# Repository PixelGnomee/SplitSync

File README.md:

# SplitSync
 83 key keyboard that is splitable

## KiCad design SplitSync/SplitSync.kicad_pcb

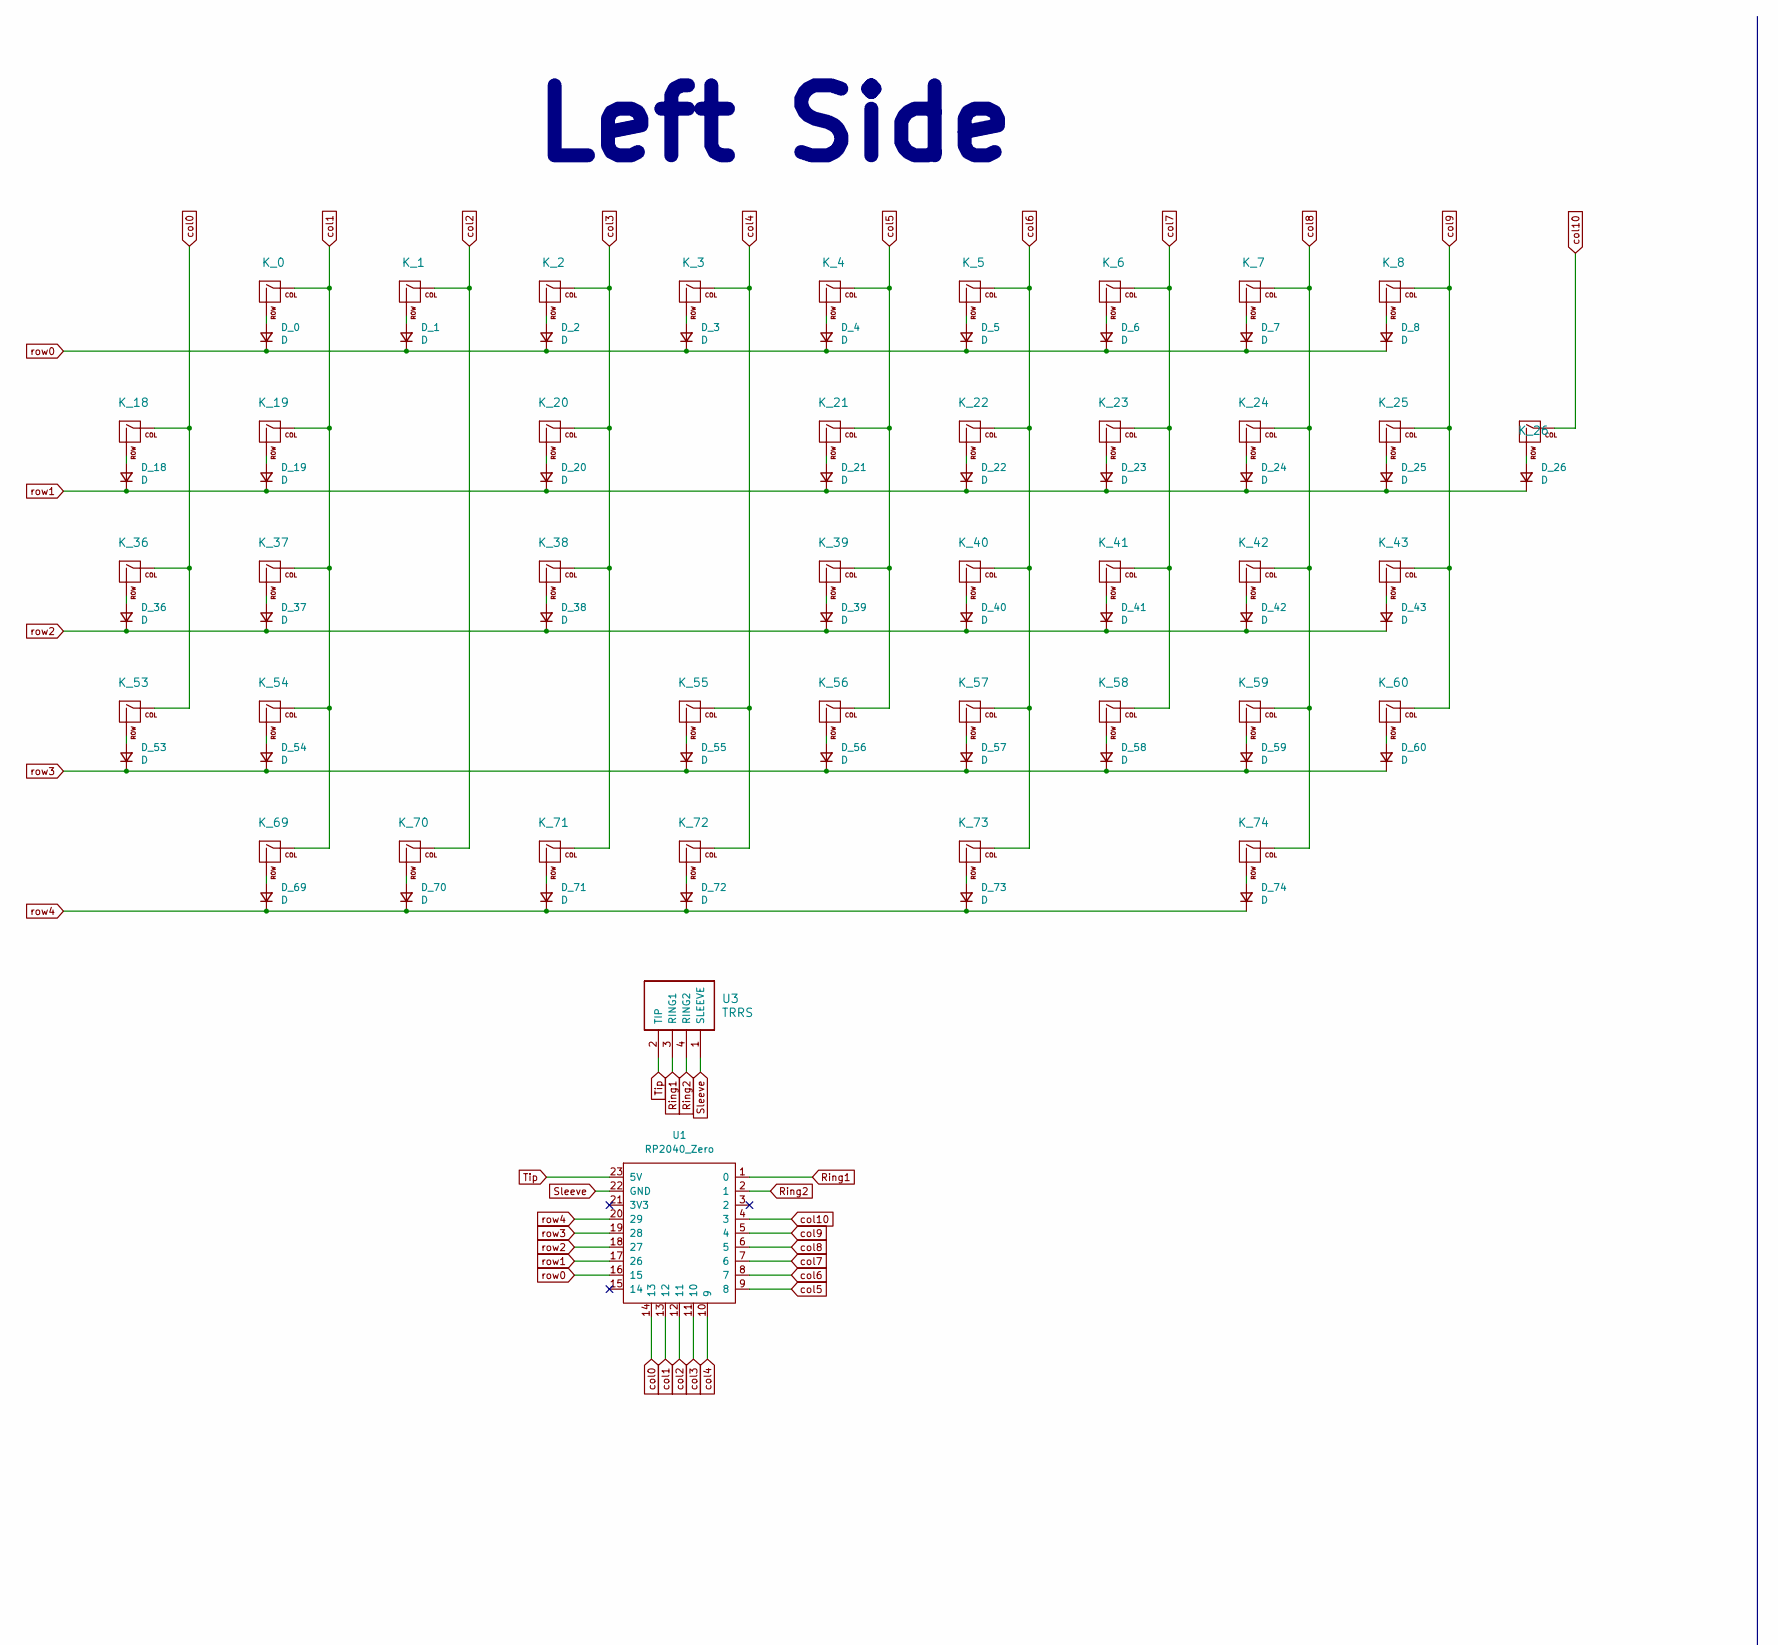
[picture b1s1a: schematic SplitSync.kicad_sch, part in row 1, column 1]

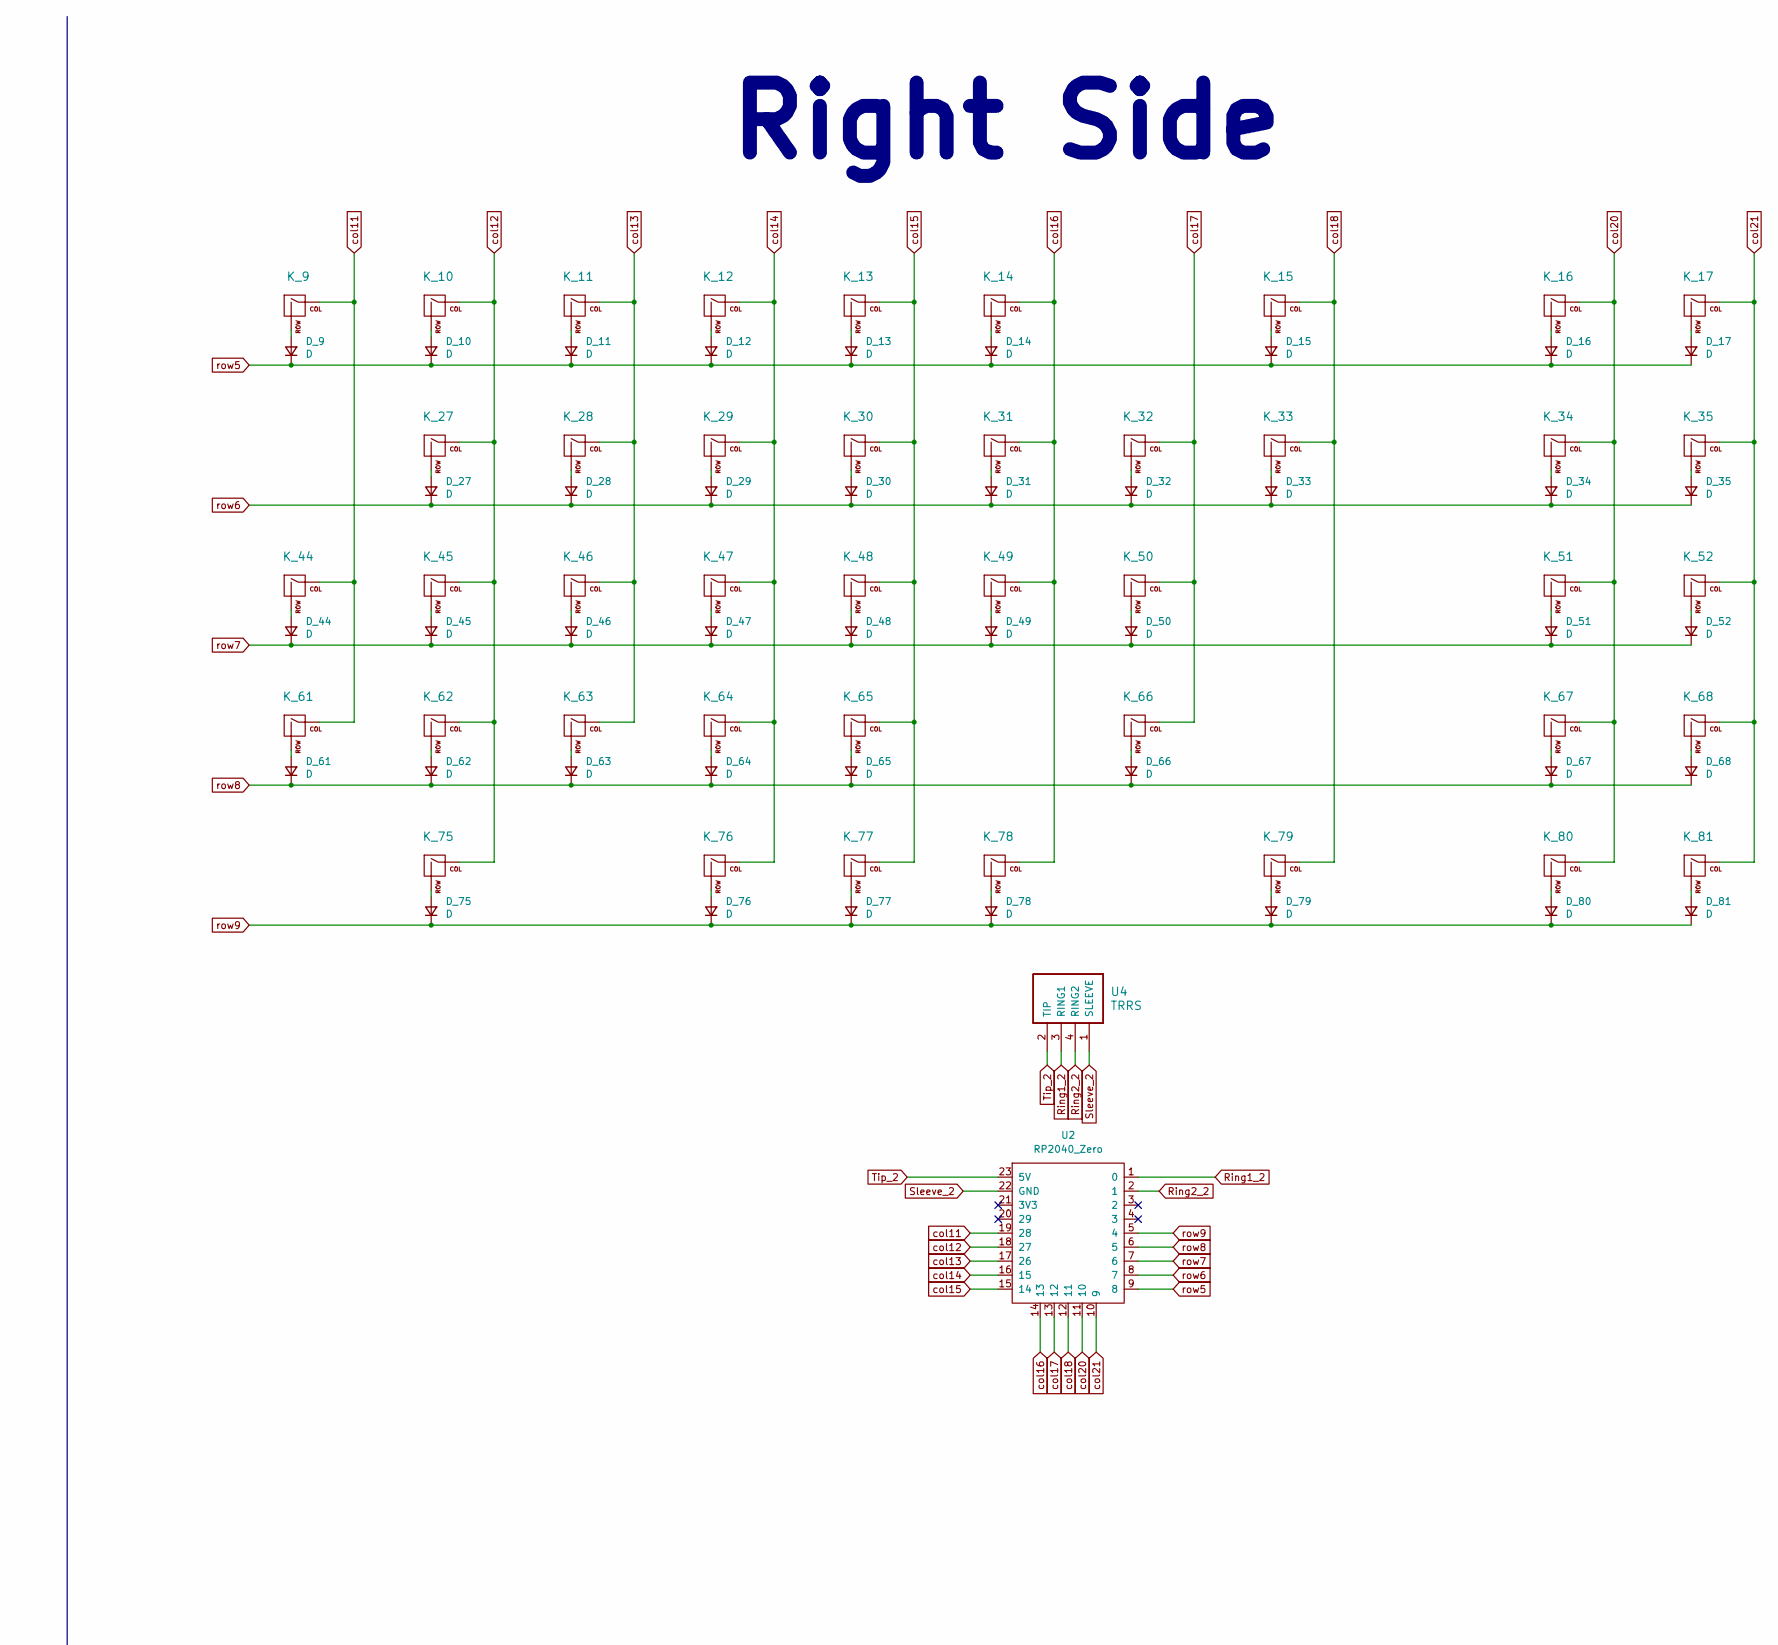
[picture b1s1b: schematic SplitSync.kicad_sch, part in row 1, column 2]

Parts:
D_0, D_1, D_2, D_3, D_4, D_5, D_6, D_7, D_8, D_9, D_10, D_11, D_12, D_13, D_14, D_15, D_16, D_17, D_18, D_19, D_20, D_21, D_22, D_23, D_24, D_25, D_26, D_27, D_28, D_29, D_30, D_31, D_32, D_33, D_34, D_35, D_36, D_37, D_38, D_39, D_40, D_41, D_42, D_43, D_44, D_45, D_46, D_47, D_48, D_49, D_50, D_51, D_52, D_53, D_54, D_55, D_56, D_57, D_58, D_59, D_60, D_61, D_62, D_63, D_64, D_65, D_66, D_67, D_68, D_69, D_70, D_71, D_72, D_73, D_74, D_75, D_76, D_77, D_78, D_79, D_80, D_81: D; D_SOD-123
K_0, K_1, K_2, K_3, K_4, K_5, K_6, K_7, K_8, K_9, K_10, K_11, K_12, K_13, K_14, K_15, K_16, K_17, K_18, K_19, K_21, K_22, K_23, K_24, K_25, K_26, K_27, K_28, K_29, K_30, K_31, K_32, K_34, K_35, K_36, K_37, K_39, K_40, K_41, K_42, K_43, K_44, K_45, K_46, K_47, K_48, K_49, K_51, K_52, K_53, K_54, K_56, K_57, K_58, K_59, K_60, K_61, K_62, K_63, K_64, K_65, K_67, K_68, K_69, K_70, K_80, K_81: KEYSW; Hotswap_MX_Plated_1.00u
K_20, K_33, K_79: KEYSW; Hotswap_MX_Plated_1.50u
K_38: KEYSW; Hotswap_MX_Plated_1.75u
K_50, K_55: KEYSW; Hotswap_MX_Plated_2.25u
K_66: KEYSW; Hotswap_MX_Plated_2.75u
K_71, K_72, K_73, K_76, K_77, K_78: KEYSW; Hotswap_MX_Plated_1.25u
K_74, K_75: KEYSW; Hotswap_MX_Plated_3.00u
U1, U2: RP2040_Zero
U3, U4: TRRS; TRRS_PJ-320A

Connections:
unnamed: D_0.2 (A), K_0.2 (ROW)
unnamed: D_1.2 (A), K_1.2 (ROW)
unnamed: D_2.2 (A), K_2.2 (ROW)
unnamed: D_3.2 (A), K_3.2 (ROW)
unnamed: D_4.2 (A), K_4.2 (ROW)
unnamed: D_5.2 (A), K_5.2 (ROW)
unnamed: D_6.2 (A), K_6.2 (ROW)
unnamed: D_7.2 (A), K_7.2 (ROW)
unnamed: D_8.2 (A), K_8.2 (ROW)
unnamed: D_9.2 (A), K_9.2 (ROW)
unnamed: D_10.2 (A), K_10.2 (ROW)
unnamed: D_11.2 (A), K_11.2 (ROW)
unnamed: D_12.2 (A), K_12.2 (ROW)
unnamed: D_13.2 (A), K_13.2 (ROW)
unnamed: D_14.2 (A), K_14.2 (ROW)
unnamed: D_15.2 (A), K_15.2 (ROW)
unnamed: D_16.2 (A), K_16.2 (ROW)
unnamed: D_17.2 (A), K_17.2 (ROW)
unnamed: D_18.2 (A), K_18.2 (ROW)
unnamed: D_19.2 (A), K_19.2 (ROW)
unnamed: D_20.2 (A), K_20.2 (ROW)
unnamed: D_21.2 (A), K_21.2 (ROW)
unnamed: D_22.2 (A), K_22.2 (ROW)
unnamed: D_23.2 (A), K_23.2 (ROW)
unnamed: D_24.2 (A), K_24.2 (ROW)
unnamed: D_25.2 (A), K_25.2 (ROW)
unnamed: D_26.2 (A), K_26.2 (ROW)
unnamed: D_27.2 (A), K_27.2 (ROW)
unnamed: D_28.2 (A), K_28.2 (ROW)
unnamed: D_29.2 (A), K_29.2 (ROW)
unnamed: D_30.2 (A), K_30.2 (ROW)
unnamed: D_31.2 (A), K_31.2 (ROW)
unnamed: D_32.2 (A), K_32.2 (ROW)
unnamed: D_33.2 (A), K_33.2 (ROW)
unnamed: D_34.2 (A), K_34.2 (ROW)
unnamed: D_35.2 (A), K_35.2 (ROW)
unnamed: D_36.2 (A), K_36.2 (ROW)
unnamed: D_37.2 (A), K_37.2 (ROW)
unnamed: D_38.2 (A), K_38.2 (ROW)
unnamed: D_39.2 (A), K_39.2 (ROW)
unnamed: D_40.2 (A), K_40.2 (ROW)
unnamed: D_41.2 (A), K_41.2 (ROW)
unnamed: D_42.2 (A), K_42.2 (ROW)
unnamed: D_43.2 (A), K_43.2 (ROW)
unnamed: D_44.2 (A), K_44.2 (ROW)
unnamed: D_45.2 (A), K_45.2 (ROW)
unnamed: D_46.2 (A), K_46.2 (ROW)
unnamed: D_47.2 (A), K_47.2 (ROW)
unnamed: D_48.2 (A), K_48.2 (ROW)
unnamed: D_49.2 (A), K_49.2 (ROW)
unnamed: D_50.2 (A), K_50.2 (ROW)
unnamed: D_51.2 (A), K_51.2 (ROW)
unnamed: D_52.2 (A), K_52.2 (ROW)
unnamed: D_53.2 (A), K_53.2 (ROW)
unnamed: D_54.2 (A), K_54.2 (ROW)
unnamed: D_55.2 (A), K_55.2 (ROW)
unnamed: D_56.2 (A), K_56.2 (ROW)
unnamed: D_57.2 (A), K_57.2 (ROW)
unnamed: D_58.2 (A), K_58.2 (ROW)
unnamed: D_59.2 (A), K_59.2 (ROW)
unnamed: D_60.2 (A), K_60.2 (ROW)
unnamed: D_61.2 (A), K_61.2 (ROW)
unnamed: D_62.2 (A), K_62.2 (ROW)
unnamed: D_63.2 (A), K_63.2 (ROW)
unnamed: D_64.2 (A), K_64.2 (ROW)
unnamed: D_65.2 (A), K_65.2 (ROW)
unnamed: D_66.2 (A), K_66.2 (ROW)
unnamed: D_67.2 (A), K_67.2 (ROW)
unnamed: D_68.2 (A), K_68.2 (ROW)
unnamed: D_69.2 (A), K_69.2 (ROW)
unnamed: D_70.2 (A), K_70.2 (ROW)
unnamed: D_71.2 (A), K_71.2 (ROW)
unnamed: D_72.2 (A), K_72.2 (ROW)
unnamed: D_73.2 (A), K_73.2 (ROW)
unnamed: D_74.2 (A), K_74.2 (ROW)
unnamed: D_75.2 (A), K_75.2 (ROW)
unnamed: D_76.2 (A), K_76.2 (ROW)
unnamed: D_77.2 (A), K_77.2 (ROW)
unnamed: D_78.2 (A), K_78.2 (ROW)
unnamed: D_79.2 (A), K_79.2 (ROW)
unnamed: D_80.2 (A), K_80.2 (ROW)
unnamed: D_81.2 (A), K_81.2 (ROW)
Ring1: U1.1 (0), U3.3 (RING1)
Ring1_2: U2.1 (0), U4.3 (RING1)
Ring2: U1.2 (1), U3.4 (RING2)
Ring2_2: U2.2 (1), U4.4 (RING2)
Sleeve: U1.22 (GND), U3.1 (SLEEVE)
Sleeve_2: U2.22 (GND), U4.1 (SLEEVE)
Tip: U1.23 (5V), U3.2 (TIP)
Tip_2: U2.23 (5V), U4.2 (TIP)
col0: K_18.1 (COL), K_36.1 (COL), K_53.1 (COL), U1.14 (13)
col1: K_0.1 (COL), K_19.1 (COL), K_37.1 (COL), K_54.1 (COL), K_69.1 (COL), U1.13 (12)
col2: K_1.1 (COL), K_70.1 (COL), U1.12 (11)
col3: K_2.1 (COL), K_20.1 (COL), K_38.1 (COL), K_71.1 (COL), U1.11 (10)
col4: K_3.1 (COL), K_55.1 (COL), K_72.1 (COL), U1.10 (9)
col5: K_4.1 (COL), K_21.1 (COL), K_39.1 (COL), K_56.1 (COL), U1.9 (8)
col6: K_5.1 (COL), K_22.1 (COL), K_40.1 (COL), K_57.1 (COL), K_73.1 (COL), U1.8 (7)
col7: K_6.1 (COL), K_23.1 (COL), K_41.1 (COL), K_58.1 (COL), U1.7 (6)
col8: K_7.1 (COL), K_24.1 (COL), K_42.1 (COL), K_59.1 (COL), K_74.1 (COL), U1.6 (5)
col9: K_8.1 (COL), K_25.1 (COL), K_43.1 (COL), K_60.1 (COL), U1.5 (4)
col10: K_26.1 (COL), U1.4 (3)
col11: K_9.1 (COL), K_44.1 (COL), K_61.1 (COL), U2.19 (28)
col12: K_10.1 (COL), K_27.1 (COL), K_45.1 (COL), K_62.1 (COL), K_75.1 (COL), U2.18 (27)
col13: K_11.1 (COL), K_28.1 (COL), K_46.1 (COL), K_63.1 (COL), U2.17 (26)
col14: K_12.1 (COL), K_29.1 (COL), K_47.1 (COL), K_64.1 (COL), K_76.1 (COL), U2.16 (15)
col15: K_13.1 (COL), K_30.1 (COL), K_48.1 (COL), K_65.1 (COL), K_77.1 (COL), U2.15 (14)
col16: K_14.1 (COL), K_31.1 (COL), K_49.1 (COL), K_78.1 (COL), U2.14 (13)
col17: K_32.1 (COL), K_50.1 (COL), K_66.1 (COL), U2.13 (12)
col18: K_15.1 (COL), K_33.1 (COL), K_79.1 (COL), U2.12 (11)
col20: K_16.1 (COL), K_34.1 (COL), K_51.1 (COL), K_67.1 (COL), K_80.1 (COL), U2.11 (10)
col21: K_17.1 (COL), K_35.1 (COL), K_52.1 (COL), K_68.1 (COL), K_81.1 (COL), U2.10 (9)
row0: D_0.1 (K), D_1.1 (K), D_2.1 (K), D_3.1 (K), D_4.1 (K), D_5.1 (K), D_6.1 (K), D_7.1 (K), D_8.1 (K), U1.16 (15)
row1: D_18.1 (K), D_19.1 (K), D_20.1 (K), D_21.1 (K), D_22.1 (K), D_23.1 (K), D_24.1 (K), D_25.1 (K), D_26.1 (K), U1.17 (26)
row2: D_36.1 (K), D_37.1 (K), D_38.1 (K), D_39.1 (K), D_40.1 (K), D_41.1 (K), D_42.1 (K), D_43.1 (K), U1.18 (27)
row3: D_53.1 (K), D_54.1 (K), D_55.1 (K), D_56.1 (K), D_57.1 (K), D_58.1 (K), D_59.1 (K), D_60.1 (K), U1.19 (28)
row4: D_69.1 (K), D_70.1 (K), D_71.1 (K), D_72.1 (K), D_73.1 (K), D_74.1 (K), U1.20 (29)
row5: D_9.1 (K), D_10.1 (K), D_11.1 (K), D_12.1 (K), D_13.1 (K), D_14.1 (K), D_15.1 (K), D_16.1 (K), D_17.1 (K), U2.9 (8)
row6: D_27.1 (K), D_28.1 (K), D_29.1 (K), D_30.1 (K), D_31.1 (K), D_32.1 (K), D_33.1 (K), D_34.1 (K), D_35.1 (K), U2.8 (7)
row7: D_44.1 (K), D_45.1 (K), D_46.1 (K), D_47.1 (K), D_48.1 (K), D_49.1 (K), D_50.1 (K), D_51.1 (K), D_52.1 (K), U2.7 (6)
row8: D_61.1 (K), D_62.1 (K), D_63.1 (K), D_64.1 (K), D_65.1 (K), D_66.1 (K), D_67.1 (K), D_68.1 (K), U2.6 (5)
row9: D_75.1 (K), D_76.1 (K), D_77.1 (K), D_78.1 (K), D_79.1 (K), D_80.1 (K), D_81.1 (K), U2.5 (4)

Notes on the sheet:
Left Side
Right Side

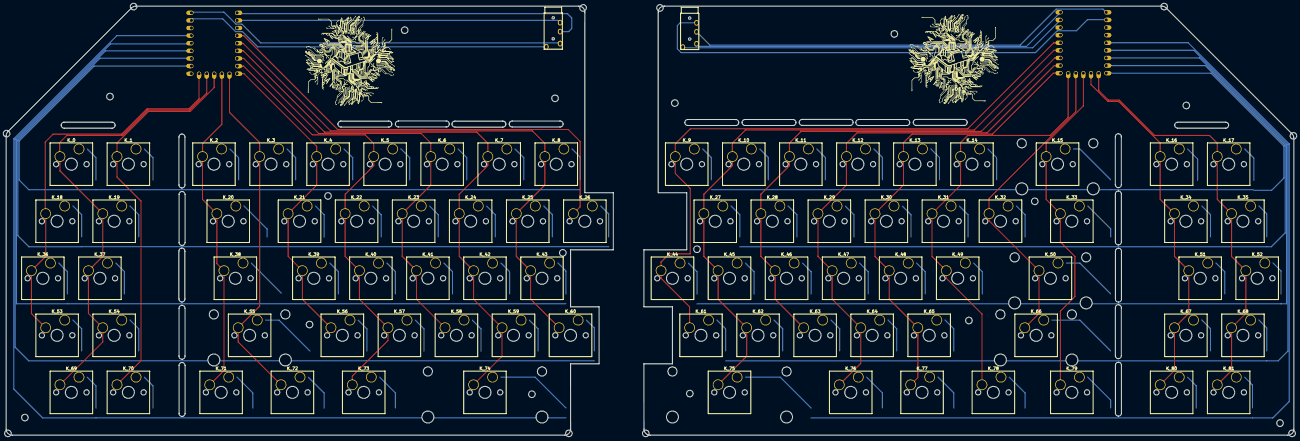
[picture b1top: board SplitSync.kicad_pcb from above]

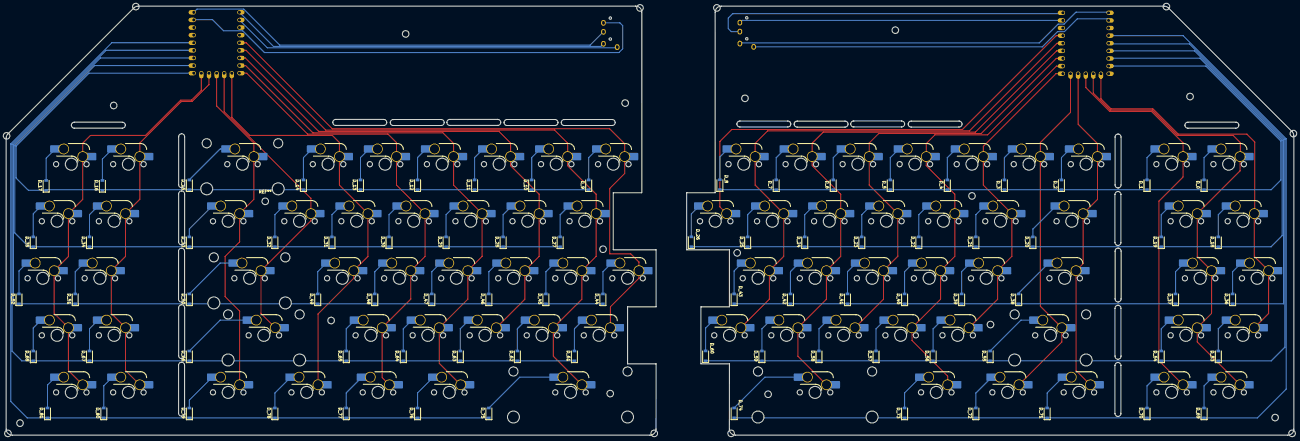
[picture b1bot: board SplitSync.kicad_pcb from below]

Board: 2 copper layers, 430.0 x 143.2 mm, 168 parts (82 on the bottom side), 121 nets.

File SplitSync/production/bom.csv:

Designator,Footprint,Quantity,Value,LCSC Part #
"D_0, D_1, D_10, D_11, D_12, D_13, D_14, D_15, D_16, D_17, D_18, D_19, D_2, D_20, D_21, D_22, D_23, D_24, D_25, D_26, D_27, D_28, D_29, D_3, D_30, D_31, D_32, D_33, D_34, D_35, D_36, D_37, D_38, D_39, D_4, D_40, D_41, D_42, D_43, D_44, D_45, D_46, D_47, D_48, D_49, D_5, D_50, D_51, D_52, D_53, D_54, D_55, D_56, D_57, D_58, D_59, D_6, D_60, D_61, D_62, D_63, D_64, D_65, D_66, D_67, D_68, D_69, D_7, D_70, D_71, D_72, D_73, D_74, D_75, D_76, D_77, D_78, D_79, D_8, D_80, D_81, D_9",D_SOD-123,82,D,
"K_0, K_1, K_10, K_11, K_12, K_13, K_14, K_15, K_16, K_17, K_18, K_19, K_2, K_21, K_22, K_23, K_24, K_25, K_26, K_27, K_28, K_29, K_3, K_30, K_31, K_32, K_34, K_35, K_36, K_37, K_39, K_4, K_40, K_41, K_42, K_43, K_44, K_45, K_46, K_47, K_48, K_49, K_5, K_51, K_52, K_53, K_54, K_56, K_57, K_58, K_59, K_6, K_60, K_61, K_62, K_63, K_64, K_65, K_67, K_68, K_69, K_7, K_70, K_8, K_80, K_81, K_9",Hotswap_MX_Plated_1.00u,67,KEYSW,
"K_20, K_33, K_79",Hotswap_MX_Plated_1.50u,3,KEYSW,
K_38,Hotswap_MX_Plated_1.75u,1,KEYSW,
"K_50, K_55",Hotswap_MX_Plated_2.25u,2,KEYSW,
K_66,Hotswap_MX_Plated_2.75u,1,KEYSW,
"K_71, K_72, K_73, K_76, K_77, K_78",Hotswap_MX_Plated_1.25u,6,KEYSW,
"K_74, K_75",Hotswap_MX_Plated_3.00u,2,KEYSW,
"U1, U2",RP2040_Zero,2,RP2040_Zero,
"U3, U4",TRRS_PJ-320A,2,TRRS,

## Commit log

2024-03-27 Initialize project
2024-03-29 oops
2024-03-29 schematic for keyboard switches layout done.
2024-03-30 layout setup entered and footprints assigned
2024-03-30 components laid out.
2024-03-30 Internalized wiring done.
2024-03-31 mounting holes placed
2024-03-31 Logo added onto board
2024-03-31 Flex Cuts
2024-03-31 final overview done
2024-04-01 guide holes set for case building phase
2024-04-01 exported step file
2024-04-01 autosave
